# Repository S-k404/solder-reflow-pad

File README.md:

<!-- datasheet:banner -->
<p align="center">
  <picture>
    <source media="(prefers-color-scheme: dark)" srcset=".github/assets/banner-dark.svg">
    
  </picture>
</p>
<!-- /datasheet:banner -->

# Solder Reflow Pad & Hotplate PCB (KiCad)

A custom open-source KiCad printed circuit board designed for miniature SMD solder reflow, hotplate prototyping, and hardware assembly with custom top and bottom silkscreen artwork.

---

<!-- datasheet:figure -->
## At a glance

<p align="center">
  <picture>
    <source media="(prefers-color-scheme: dark)" srcset=".github/assets/diagram-dark.svg">
    
  </picture>
</p>
<!-- /datasheet:figure -->

## 🛠️ Overview & Architecture

This project provides a compact PCB hotplate design tailored for reflowing surface-mount devices (SMD), desoldering small ICs, and prototyping on a workbench.

- **CAD Suite**: Designed in **KiCad 10** (`.kicad_pcb`, `.kicad_sch`, `.kicad_pro`).
- **Layers**: 2-layer design (`F.Cu` / `B.Cu`) with standard 1.6mm board thickness (compatible with aluminum core substrate or standard FR-4).
- **Integrated Heating Element**: Custom `1MM_HOT_PLATE` layout engineered for controlled thermal dissipation.
- **Circuitry & Footprints**:
  - `SOIC127P600X175-14N` footprint for control and logic.
  - Standard `0805` and `1206` passive footprints for current limiting and decoupling capacitors.
  - Multi-pin headers (`MA03-1`, `MA04-1`, `1X03`) for power input, thermistor/thermocouple sensing, and external MCU telemetry.
  - Custom high-contrast silkscreen typography (`V4`) and reference indicators.

---

## 📐 Board Specifications

| Parameter | Specification |
| :--- | :--- |
| **Board Dimensions** | Standard bench form factor with M3 mounting holes |
| **Layer Count** | 2 Layers (`F.Cu`, `B.Cu`) |
| **Base Material** | FR-4 (or Aluminum Metal Core PCB / IMS for superior heat distribution) |
| **Finished Thickness** | 1.6 mm |
| **Recommended Copper** | **2 oz (70 µm)** minimum recommended for heating traces |
| **Surface Finish** | **ENIG (Electroless Nickel Immersion Gold)** for oxidation resistance at reflow temperatures |
| **Solder Mask** | High-temperature matte black or white |

---

## 📂 Project Structure

```
Solder Reflow Pad Silkscreen/
├── Solder Refow Pad Silkscreen.kicad_pcb   # Complete routed PCB layout & thermal geometry
├── Solder Refow Pad Silkscreen.kicad_sch   # Schematic design file
├── Solder Refow Pad Silkscreen.kicad_pro   # KiCad project definition
├── .gitignore                              # Clean repo exclusions
└── README.md                               # Hardware documentation & fabrication guidelines
```

---

## ⚡ Fabrication & Assembly Recommendations

1. **Substrate Selection**: For maximum thermal conductivity and rapid, even heat spread, export Gerbers and order as an **Aluminum Core PCB (MCPCB)**. If manufactured on standard FR-4, keep peak temperatures within rated limits (<240°C for lead-free SAC305 reflow profiles).
2. **Thermal Sensor**: Solder an NTC thermistor (or K-type thermocouple probe) directly to the designated sensing pads with high-temperature silicone or Kapton tape to ensure accurate closed-loop PID control.
3. **Power Delivery**: Use thick gauge wire (16–18 AWG silicon wire) for power delivery connections to minimize resistive losses across header pins.

---

## 📄 License

Open Hardware design released under the **CERN Open Hardware Licence Version 2 - Permissive (CERN-OHL-P)** or MIT.

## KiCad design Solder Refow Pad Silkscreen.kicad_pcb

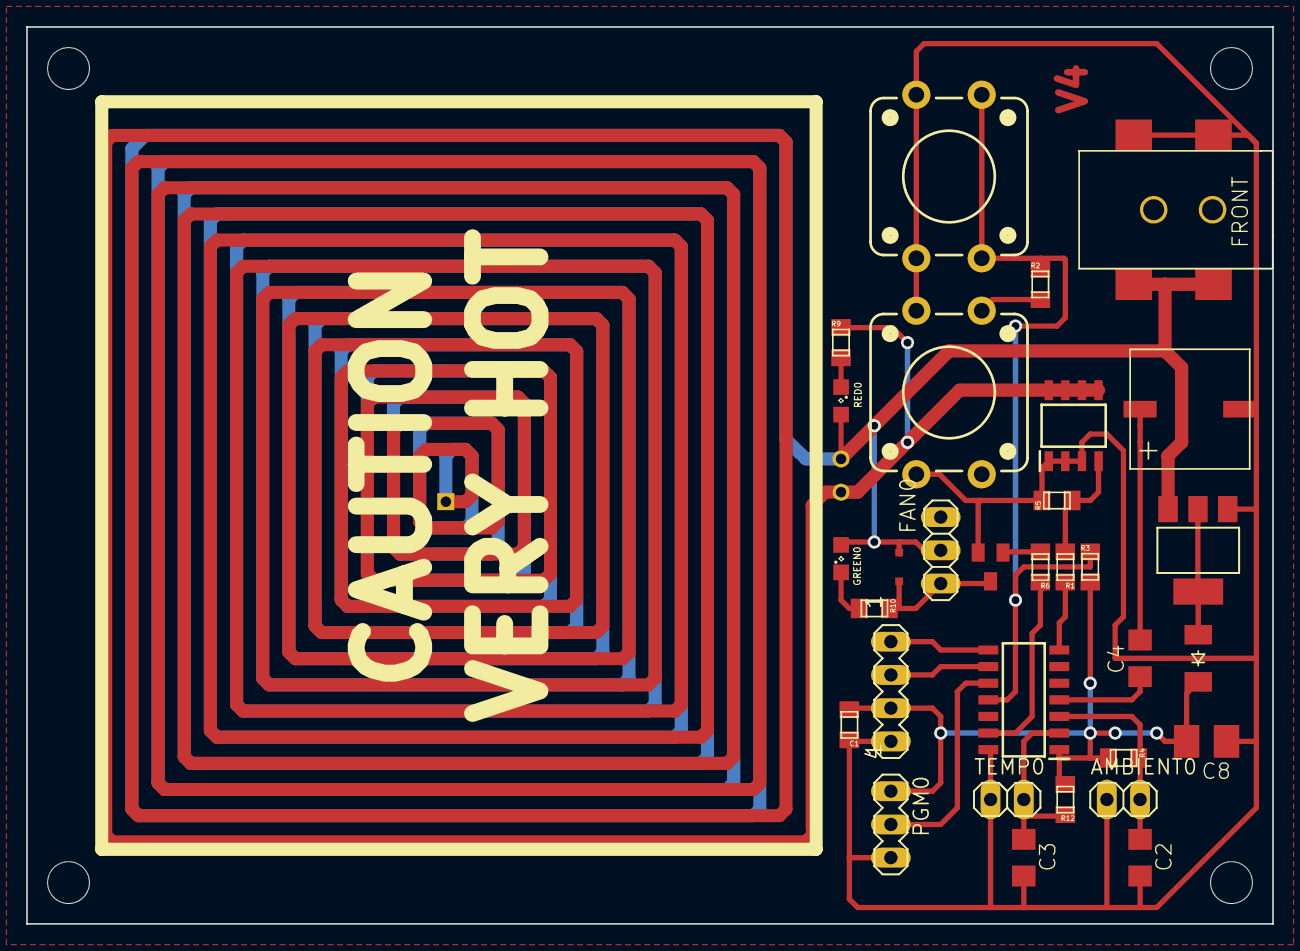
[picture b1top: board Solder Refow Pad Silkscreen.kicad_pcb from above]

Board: 2 copper layers, 95.2 x 68.6 mm, 36 parts (0 on the bottom side), 21 nets.

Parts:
AMBIENT0: 1X02
C1: 0.1uF; C0805.5
C2, C3, C4: 10uF; C1206
C8: 47/16; B_3528-21R
D1: 1N4148; SOD323-R
D2: 1N4007; SOD-123_MINI-SMA
FAN0: 1X03
GREEN0: SML0805
IC1: ATTINY1614; SOIC127P600X175-14N
PGM0: MA03-1
Q1: AO4406AL; SOIC127P600X175-8N
R1, R6, R9, R10: 1K; R0805.5
R2, R3, R5: 10K; R0805.5
R4, R12: 4K7; R0805.5
RED0: SML0805
SELECT0: SWITCH_TAC_12MM
SPKR0: BUZZERSPEAKER_SMD_SQUARE; SPEAKER_SQUARE_SMD
START0: SWITCH_TAC_12MM
SV1: OLED; MA04-1
T2: 2N3904; SOT23-BEC
TEMP0: 1X02
U$1: HOT_PLATE; 1MM_HOT_PLATE
U$2: 12V; DC_SMD_TECHNIK
U$3: REG1117-50; SOT223-T
UNK_HOLE_0: dummyfp0
UNK_HOLE_1: dummyfp1
UNK_HOLE_2: dummyfp2
UNK_HOLE_3: dummyfp3

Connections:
+12V: D1.C, FAN0.2, GREEN0.A, RED0.A, U$1.P2, U$2.P$1_POS, U$2.P$1_POS1, U$3.3
AMBIENT: AMBIENT0.2, C2.1, IC1.3, R4.1
FAN: IC1.13, R6.1
GND: AMBIENT0.1, C1.1, C2.2, C3.2, C8.-, IC1.14, PGM0.3, Q1.1, Q1.2, Q1.3, R5.1, SELECT0.3, SELECT0.4, SPKR0.P$2_NEG, START0.3, START0.4, SV1.4, T2.E, TEMP0.1, U$2.P$2_NEG_SW, U$2.P$3_NEG, U$3.1
HEATER: IC1.7, R1.1
MOVE: R2.2, SELECT0.1
unnamed: C4.2, SPKR0.P$1_POS
unnamed: D1.A, FAN0.1, R10.1, T2.C
unnamed: R6.2, T2.B
unnamed: R9.2, RED0.C
unnamed: GREEN0.C, R10.2
unnamed: D2.A, U$3.2, U$3.4
unnamed: Q1.5, Q1.6, Q1.7, Q1.8, R9.1, U$1.P1
unnamed: Q1.4, R1.2, R5.2
SCL: IC1.9, SV1.2
SDA: IC1.8, SV1.1
SPEAKER: C4.1, IC1.4
SWITCHES: IC1.11, R2.1, R3.1, START0.1, START0.2
TEMP: C3.1, IC1.2, R12.1, TEMP0.2
UPDI: IC1.10, PGM0.2
VDD: C1.2, C8.+, D2.C, IC1.1, PGM0.1, R3.2, R4.2, R12.2, SV1.3
